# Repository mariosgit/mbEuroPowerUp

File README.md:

# mbEuroPowerUp

Eurorack power converter

Input: 5V

Output: +-12V

It's magic.

## Status

Works on breadboard. Waiting for PCB...

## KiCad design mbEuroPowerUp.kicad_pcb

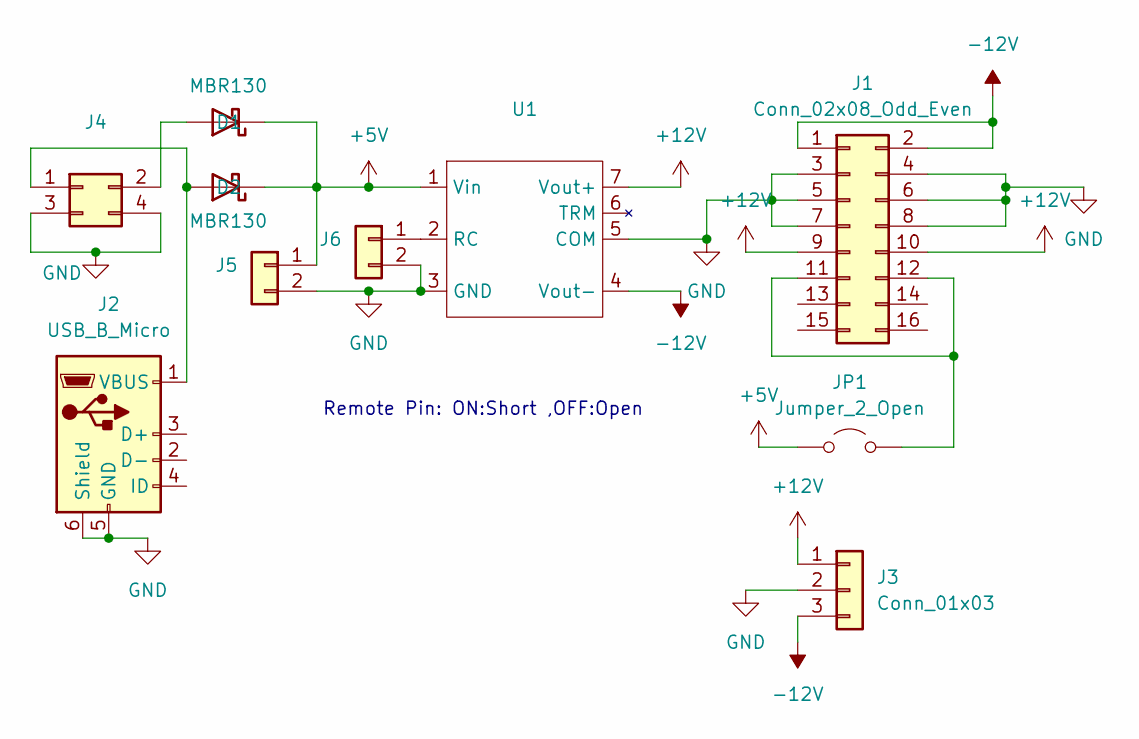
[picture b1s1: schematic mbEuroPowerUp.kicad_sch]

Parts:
D1, D2: MBR130; D_SOD-123
J1: Conn_02x08_Odd_Even; PinHeader_2x08_P2.54mm_Vertical
J2: USB_B_Micro; USB_Micro-B_Wuerth_629105150521
J3: Conn_01x03; PinHeader_1x03_P2.54mm_Vertical
J4: Conn_02x02_Odd_Even; PinHeader_2x02_P2.54mm_Vertical
J5, J6: Conn_01x02; PinHeader_1x02_P2.54mm_Vertical
JP1: Jumper_2_Open; SolderJumper-2_P1.3mm_Open_TrianglePad1.0x1.5mm
U1: TDK-CC6

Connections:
+5V: D1.1 (K), D2.1 (K), J5.1, JP1.1 (A), U1.1 (Vin)
+12V: J1.9, J1.10, J3.1, U1.7 (Vout+)
-12V: J1.1, J1.2, J3.3, U1.4 (Vout-)
GND: J1.3, J1.4, J1.5, J1.6, J1.7, J1.8, J2.5 (GND), J2.6 (Shield), J3.2, J4.3, J4.4, J5.2, J6.2, U1.3 (GND), U1.5 (COM)
unnamed: D1.2 (A), J2.1 (VBUS), J4.1
unnamed: D2.2 (A), J4.2
unnamed: J1.11, J1.12, JP1.2 (B)
unnamed: J6.1, U1.2 (RC)

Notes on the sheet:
Remote Pin: ON:Short ,OFF:Open

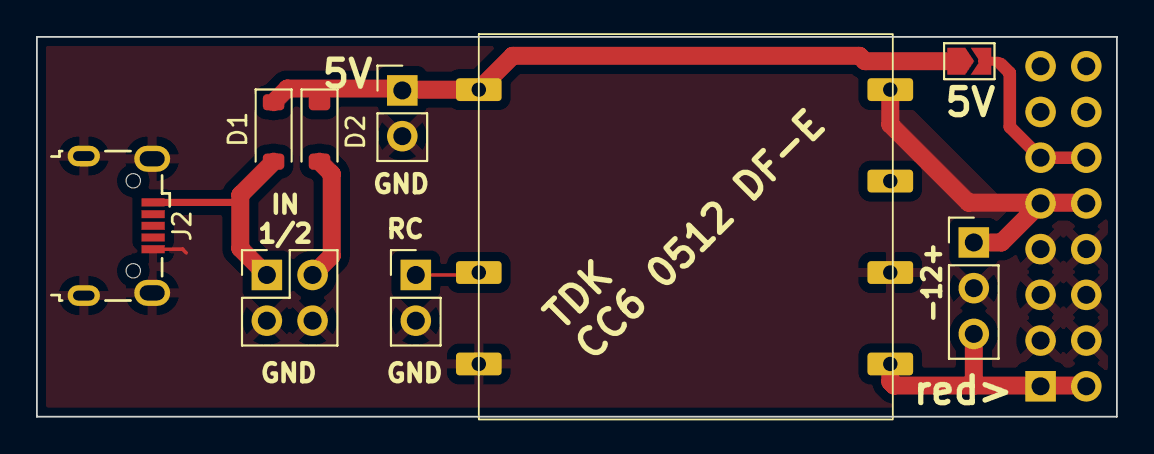
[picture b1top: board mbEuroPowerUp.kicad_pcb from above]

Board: 2 copper layers, 60.0 x 21.1 mm, 10 parts (1 on the bottom side), 8 nets.

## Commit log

2025-10-05 Fix 5V Pins
